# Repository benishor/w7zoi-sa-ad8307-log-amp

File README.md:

# w7zoi-sa-ad8307-log-amp
Kicad files for the new AD8307 log amp for W7ZOI spectrum analyzer.

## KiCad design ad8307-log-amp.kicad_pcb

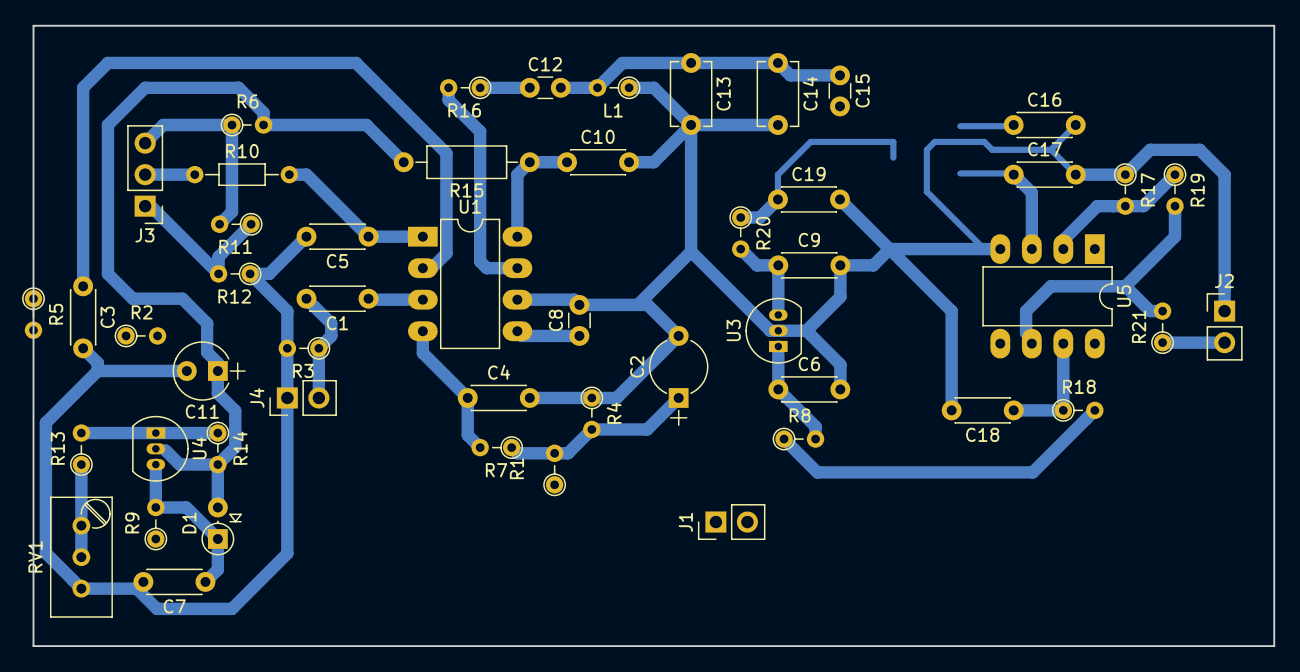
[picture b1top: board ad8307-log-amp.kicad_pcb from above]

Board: 2 copper layers, 100.0 x 50.0 mm, 52 parts (1 on the bottom side), 30 nets.

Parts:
C1: .01; C_Disc_D4.3mm_W1.9mm_P5.00mm
C2: 100u; CP_Radial_Tantal_D4.5mm_P5.00mm
C3, C4, C5, C7, C9, C10, C16, C18, C19: .1; C_Disc_D4.3mm_W1.9mm_P5.00mm
C6: .22; C_Disc_D4.3mm_W1.9mm_P5.00mm
C8: 18; C_Disc_D3.0mm_W1.6mm_P2.50mm
C11: 22u; CP_Radial_Tantal_D4.5mm_P2.50mm
C12, C15: 5.6p; C_Disc_D3.0mm_W1.6mm_P2.50mm
C13: 5-65; C_Disc_D5.1mm_W3.2mm_P5.00mm
C14: 200; C_Disc_D5.1mm_W3.2mm_P5.00mm
C17: .001; C_Disc_D4.3mm_W1.9mm_P5.00mm
D1: 1N4152; D_DO-35_SOD27_P2.54mm_Vertical_AnodeUp
J1: POWER_IN; Pin_Header_Straight_1x02_Pitch2.54mm
J2: SIGNAL_OUT; Pin_Header_Straight_1x02_Pitch2.54mm
J3: IF_GAIN; Pin_Header_Straight_1x03_Pitch2.54mm
J4: SIGNAL_IN; Pin_Header_Straight_1x02_Pitch2.54mm
L1: 1.05u; R_Axial_DIN0204_L3.6mm_D1.6mm_P2.54mm_Vertical
R1, R4, R19: 2.2K; R_Axial_DIN0204_L3.6mm_D1.6mm_P2.54mm_Vertical
R2: 4.3K; R_Axial_DIN0204_L3.6mm_D1.6mm_P2.54mm_Vertical
R3: 100; R_Axial_DIN0204_L3.6mm_D1.6mm_P2.54mm_Vertical
R5: 5.6K; R_Axial_DIN0204_L3.6mm_D1.6mm_P2.54mm_Vertical
R6, R17: 680; R_Axial_DIN0204_L3.6mm_D1.6mm_P2.54mm_Vertical
R7, R18: 51; R_Axial_DIN0204_L3.6mm_D1.6mm_P2.54mm_Vertical
R8, R9, R20: 10; R_Axial_DIN0204_L3.6mm_D1.6mm_P2.54mm_Vertical
R10: 2.2K; R_Axial_DIN0204_L3.6mm_D1.6mm_P7.62mm_Horizontal
R11: 510; R_Axial_DIN0204_L3.6mm_D1.6mm_P2.54mm_Vertical
R12, R16, R21: 1K; R_Axial_DIN0204_L3.6mm_D1.6mm_P2.54mm_Vertical
R13: 1.5K; R_Axial_DIN0204_L3.6mm_D1.6mm_P2.54mm_Vertical
R14: 220; R_Axial_DIN0204_L3.6mm_D1.6mm_P2.54mm_Vertical
R15: 10; R_Axial_DIN0207_L6.3mm_D2.5mm_P10.16mm_Horizontal
RV1: 82; Potentiometer_Trimmer_Bourns_3296W
U1: AD603; DIP-8_W7.62mm_LongPads
U2: AD8307; SOIC-8_3.9x4.9mm_Pitch1.27mm
U3: 78L05; TO-92_Inline_Narrow_Oval
U4: LM317AT; TO-92_Inline_Narrow_Oval
U5: CA3140; DIP-8_W7.62mm_LongPads

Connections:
/+5v: C9.1, R20.2, U3.3
/+10v: C11.1, D1.2, R1.1, R2.2, R6.2, R14.2, R15.2, U4.2
/+15v: J1.2, R8.1, R9.1, R18.2
/IF_GAIN_A: J3.3, R6.1, R11.2
/IF_GAIN_B: J3.2, R10.1
/IF_GAIN_C: J3.1, R11.1, R12.2
/IN: C1.2, J4.2, R3.1
/V_OUT: J2.2, R21.1
GND: C2.2, C3.2, C4.2, C5.2, C6.2, C7.2, C8.2, C9.2, C10.2, C11.2, C13.2, C14.2, C16.2, C17.2, C18.2, C19.2, J1.1, J2.1, J4.1, L1.1, R3.2, R4.1, R5.2, R12.1, R17.1, RV1.3, U1.6, U2.2, U3.2, U5.4
unnamed: C1.1, U1.3
unnamed: C2.1, R1.2, R4.2, R7.1
unnamed: C3.1, R2.1, R5.1, U1.2
unnamed: C4.1, R7.2, U1.4
unnamed: C5.1, R10.2, U1.1
unnamed: C6.1, R8.2, U3.1
unnamed: C7.1, D1.1, R9.2, U4.3
unnamed: C8.1, U1.5
unnamed: C10.1, R15.1, U1.8
unnamed: C12.1, R16.1
unnamed: C12.2, C13.1, C14.1, C15.1, L1.2
unnamed: C15.2, U2.8
unnamed: C16.1, U2.1
unnamed: C17.1, U2.4, U5.3
unnamed: C18.1, R18.1, U5.7
unnamed: C19.1, R20.1, U2.6, U2.7
unnamed: R13.1, RV1.1, RV1.2
unnamed: R13.2, R14.1, U4.1
unnamed: R16.2, U1.7
unnamed: R17.2, R19.1, U5.2
unnamed: R19.2, R21.2, U5.6

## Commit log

2017-04-15 Added schematic and WIP pcb
